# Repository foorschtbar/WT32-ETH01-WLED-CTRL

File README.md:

# WT32-ETH01 WLED CTRL

A wired (Ethernet/LAN) WLED Controller

## Links

- [Unofficial guide to the WT32-ETH01](https://github.com/egnor/wt32-eth01)

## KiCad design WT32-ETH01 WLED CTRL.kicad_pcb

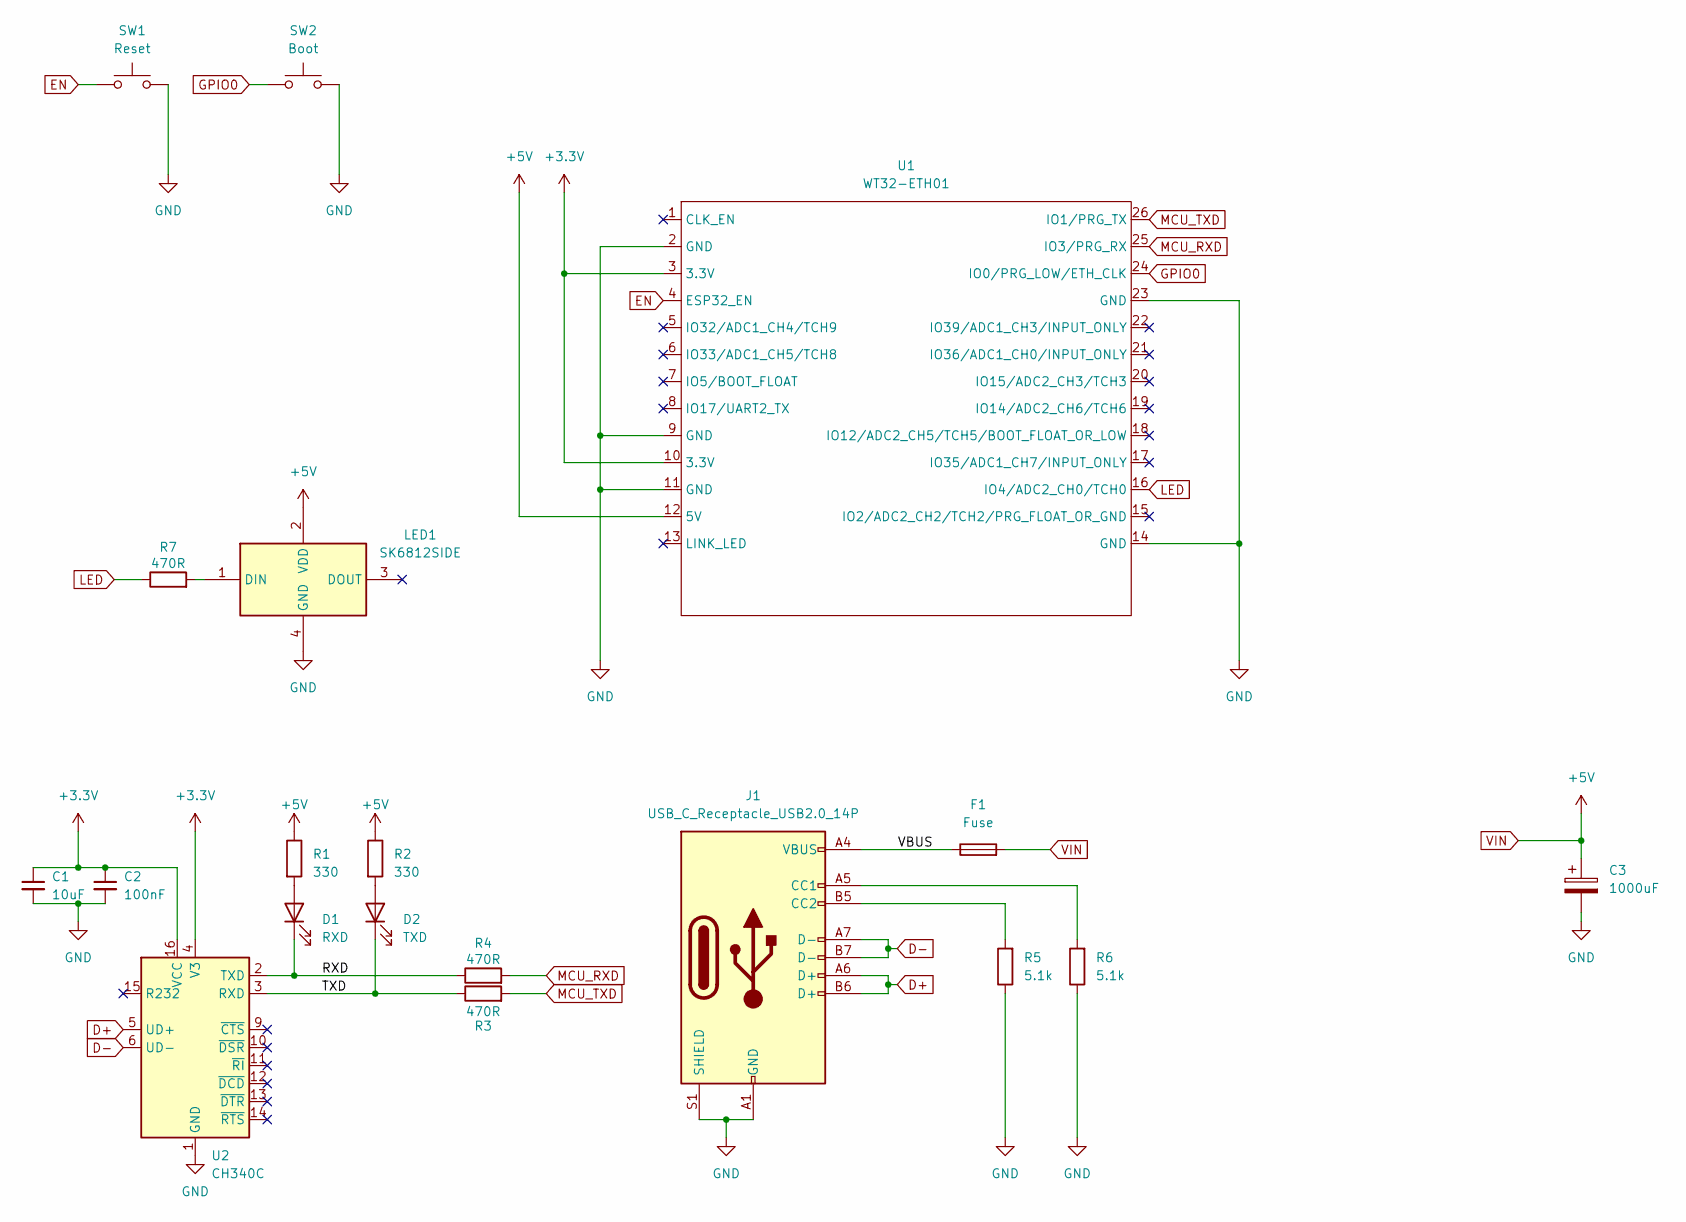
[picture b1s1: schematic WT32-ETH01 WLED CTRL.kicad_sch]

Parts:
C1: 10uF; C_0805_2012Metric_Pad1.18x1.45mm_HandSolder
C2: 100nF; C_0805_2012Metric_Pad1.18x1.45mm_HandSolder
C3: 1000uF; C_Elec_10x10.2
D1: RXD; LED_0805_2012Metric; LCSC Part # C131244
D2: TXD; LED_0805_2012Metric; LCSC Part # C131244
F1: Fuse; Fuse_0805_2012Metric_Pad1.15x1.40mm_HandSolder
J1: USB_C_Receptacle_USB2.0_14P; USB_C_Receptacle_GCT_USB4105-xx-A_16P_TopMnt_Horizontal
LED1: SK6812SIDE; Manufacturer_Part_Number SK6812SIDE
R1, R2: 330; R_0805_2012Metric_Pad1.20x1.40mm_HandSolder; LCSC Part # C17630
R3, R4, R7: 470R; R_0805_2012Metric_Pad1.20x1.40mm_HandSolder
R5, R6: 5.1k; R_0805_2012Metric_Pad1.20x1.40mm_HandSolder
SW1: Reset; Pushbutton 3x4x2mm
SW2: Boot; Pushbutton 3x4x2mm
U1: WT32-ETH01
U2: CH340C; SOIC-16_3.9x9.9mm_P1.27mm

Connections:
+3.3V: C1.1, C2.1, U1.3 (3.3V), U1.10 (3.3V), U2.4 (V3), U2.16 (VCC)
/RXD: D1.1 (K), R4.1, U2.2 (TXD)
/TXD: D2.1 (K), R3.1, U2.3 (RXD)
/VBUS: F1.1, J1.A4 (VBUS), J1.A9 (VBUS), J1.B4 (VBUS), J1.B9 (VBUS)
D+: J1.A6 (D+), J1.B6 (D+), U2.5 (UD+)
D-: J1.A7 (D-), J1.B7 (D-), U2.6 (UD-)
DTR: U2.13 (~DTR)
EN: SW1.1, U1.4 (ESP32_EN)
GND: C1.2, C2.2, C3.2, J1.A1 (GND), J1.A12 (GND), J1.B1 (GND), J1.B12 (GND), J1.S1 (SHIELD), LED1.4 (GND), R5.1, R6.1, SW1.2, SW2.2, U1.2 (GND), U1.9 (GND), U1.11 (GND), U1.14 (GND), U1.23 (GND), U2.1 (GND)
GPIO0: SW2.1, U1.24 (IO0/PRG_LOW/ETH_CLK)
LED: R7.1, U1.16 (IO4/ADC2_CH0/TCH0)
MCU_RXD: R4.2, U1.25 (IO3/PRG_RX)
MCU_TXD: R3.2, U1.26 (IO1/PRG_TX)
unnamed: D1.2 (A), R1.2
unnamed: D2.2 (A), R2.2
unnamed: J1.A5 (CC1), R6.2
unnamed: J1.B5 (CC2), R5.2
unnamed: LED1.1 (DIN), R7.2
RTS: U2.14 (~RTS)
VIN: C3.1, F1.2, LED1.2 (VDD), R1.1, R2.1, U1.12 (5V)

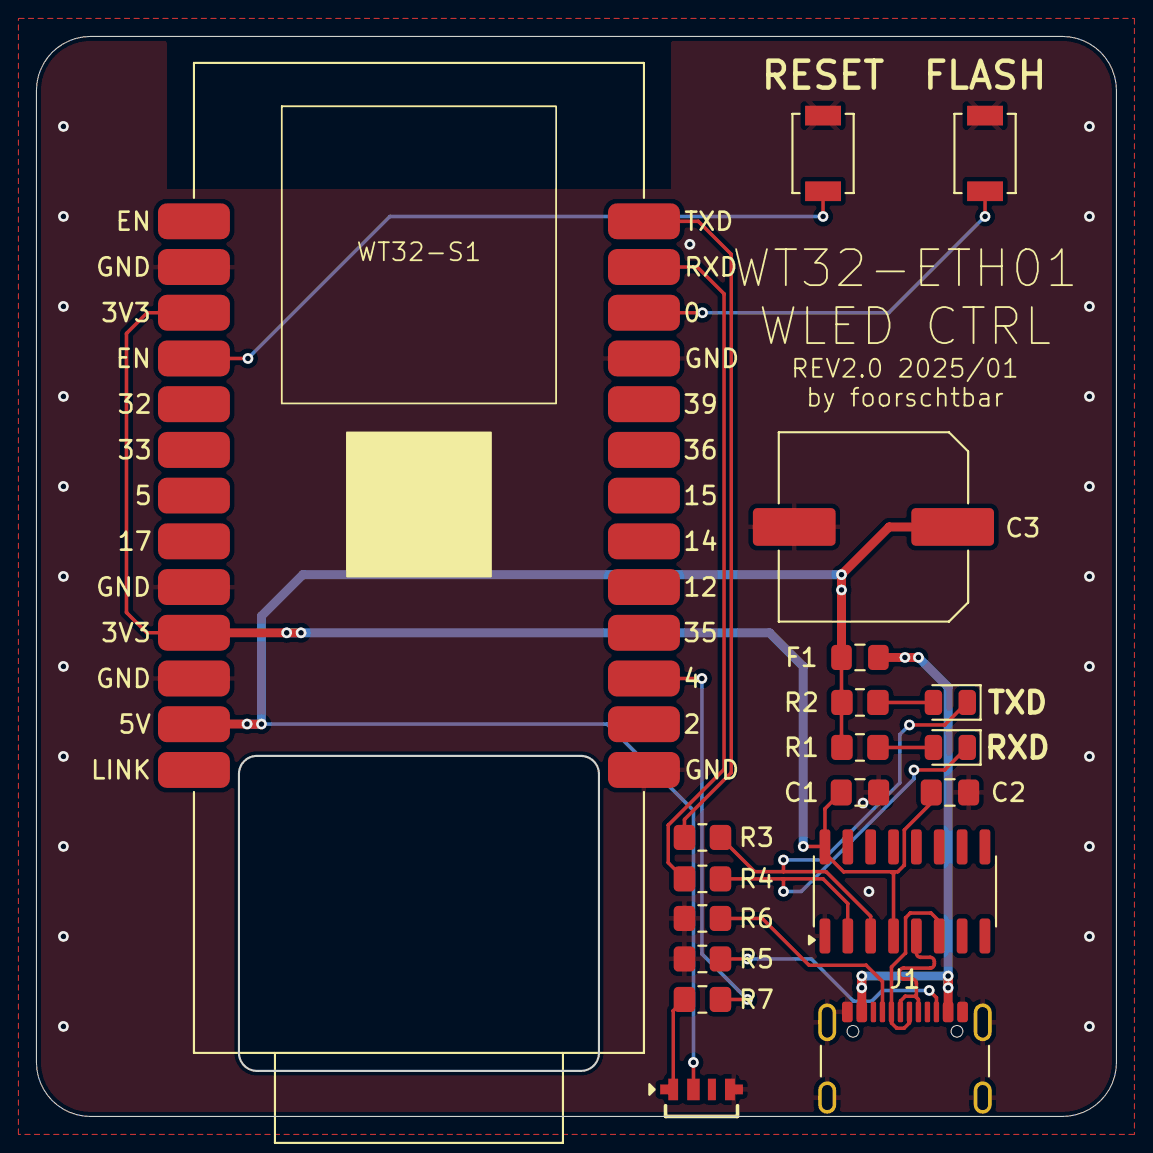
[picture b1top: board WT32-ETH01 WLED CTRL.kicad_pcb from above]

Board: 2 copper layers, 59.9 x 59.9 mm, 19 parts (0 on the bottom side), 18 nets.

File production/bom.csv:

Designator,Footprint,Quantity,Value,LCSC Part #
C1,0805,1,10uF,
C2,0805,1,100nF,
C3,C_Elec_10x10.2,1,1000uF,
D1,0805,1,RXD,C131244
D2,0805,1,TXD,C131244
F1,0805,1,Fuse,
J1,USB_C_Receptacle_GCT_USB4105-xx-A_16P_TopMnt_Horizontal,1,USB_C_Receptacle_USB2.0_14P,
LED1,SK6812SIDE,1,SK6812SIDE,
"R1, R2",0805,2,330,C17630
"R3, R4, R7",0805,3,470R,
"R5, R6",0805,2,5.1k,
SW1,Pushbutton 3x4x2mm,1,Reset,
SW2,Pushbutton 3x4x2mm,1,Boot,
U1,WT32-ETH01,1,WT32-ETH01,
U2,SOIC-16_3.9x9.9mm_P1.27mm,1,CH340C,

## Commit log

2024-12-15 README.md aktualisieren
2025-01-01 Updated Board to REV2.0 - Removed usb reset circut - Added antenna cutout - Added TX/RX LEDs
